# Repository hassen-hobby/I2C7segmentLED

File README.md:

# I2C7segmentLED

スレーブアドレスは0x70（0xE0）から0x7F（0xFE）までジャンパーで選べます。<br>
スタートコンディション、スレーブアドレスに続いて1桁目（右側）、2桁目（左側）の表示データを送ります。<br>
3バイト目以降は1桁目、2桁目と交互に上書きされます。<br>
最後にストップコンディションを送ります(送らなくても表示は更新されます)<br>
読み出しは無視されます。<br>
<br>
<br>
データの並び順はMSBから<br>
DP. a b c d e f g
です。
<br>
16進数(0-F)を表示する場合のデータ<br>
    const unsigned char seg[16]={<br>
    0x7E,0x30,0x6D,0x79,0x33,0x5B,0x5F,0x70,0x7F,0x7B,0x77,0x1F,0x0D,0x3D,0x4F,0x47<br>
    };<br>
<br>
.zipは回路図と基板データ<br>

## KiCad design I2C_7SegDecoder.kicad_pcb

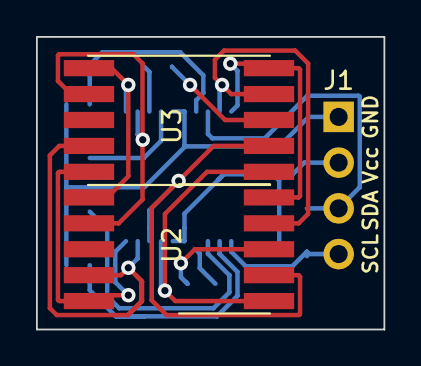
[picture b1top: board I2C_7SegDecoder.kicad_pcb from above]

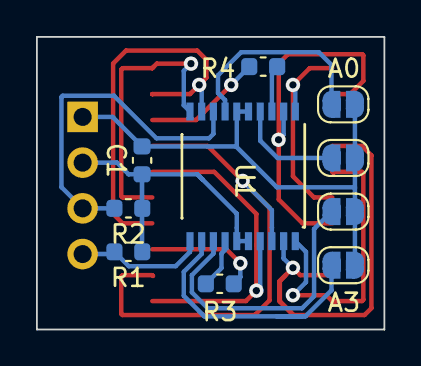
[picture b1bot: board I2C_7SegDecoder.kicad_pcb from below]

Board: 2 copper layers, 19.3 x 16.3 mm, 13 parts (10 on the bottom side), 20 nets.

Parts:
 : Jumper_NO_Small; SolderJumper-2_P1.3mm_Open_RoundedPad1.0x1.5mm
 #2: Jumper_NO_Small; SolderJumper-2_P1.3mm_Open_RoundedPad1.0x1.5mm
A0, A3: Jumper_NO_Small; SolderJumper-2_P1.3mm_Open_RoundedPad1.0x1.5mm
C1: C; C_0603_1608Metric
J1: Conn_01x04; PinHeader_1x04_P2.54mm_Horizontal
R1, R2, R3, R4: R; C_0603_1608Metric
U1: PIC16F1827-SSOP; SSOP-20_4.4x6.5mm_P0.65mm
U2, U3: GS2020CB-A; KCSC02-105

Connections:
/7SEG_C1: R3.1, U1.14
/7SEG_C2: R4.1, U1.3
/7SEG_DP: U1.10, U2.5, U3.5
/7SEG_a: U1.2, U2.7, U3.7
/7SEG_b: U1.1, U2.6, U3.6
/7SEG_c: U1.9, U2.4, U3.4
/7SEG_d: U1.18, U2.2, U3.2
/7SEG_e: U1.17, U2.1, U3.1
/7SEG_f: U1.19, U2.9, U3.9
/7SEG_g: U1.20, U2.10, U3.10
/A0: A0.1, U1.7
/A1: #2.1, U1.4
/A2: .1, U1.13
/A3: A3.1, U1.12
/SCL: J1.4, R1.2, U1.11
/SDA: J1.3, R2.2, U1.8
GND: .2, #2.2, A0.2, A3.2, C1.2, J1.1, U1.5, U1.6
unnamed: R3.2, U2.3
unnamed: R4.2, U3.3
VCC: C1.1, J1.2, R1.1, R2.1, U1.15, U1.16
